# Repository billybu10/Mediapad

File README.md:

# Mediapad

Mediapad is an 8 key macropad with a two rotary encoders, an OLED Display. It uses QMK firmware

It focuses on media control and launching programs.

## CAD Model:
It has 2 separate printed pieces. The base where the PCB sits and the top cover.

Made in Fusion360.

## PCB
PCB made in KiCad.

Schematic

PCB

## Firmware Overview
This hackpad uses [QMK](https://qmk.fm/) firmware for everything. 

- the rotary encoders change volume and brightness
- The 8 keys
  
Mute | Play/Pause | Previous track | Next Track 
---|---|---|---
Calculator | Web browser | E-mail | Control Panel

## BOM:
Here should be everything you need to make this hackpad

- 8x Cherry MX Switches
- 8x DSA Keycaps
- 8x 1N4148 DO-35 Diodes.
- 2x EC11 Rotary Encoder
- 1x XIAO RP2040
- 1x Case (2 3d printed parts)

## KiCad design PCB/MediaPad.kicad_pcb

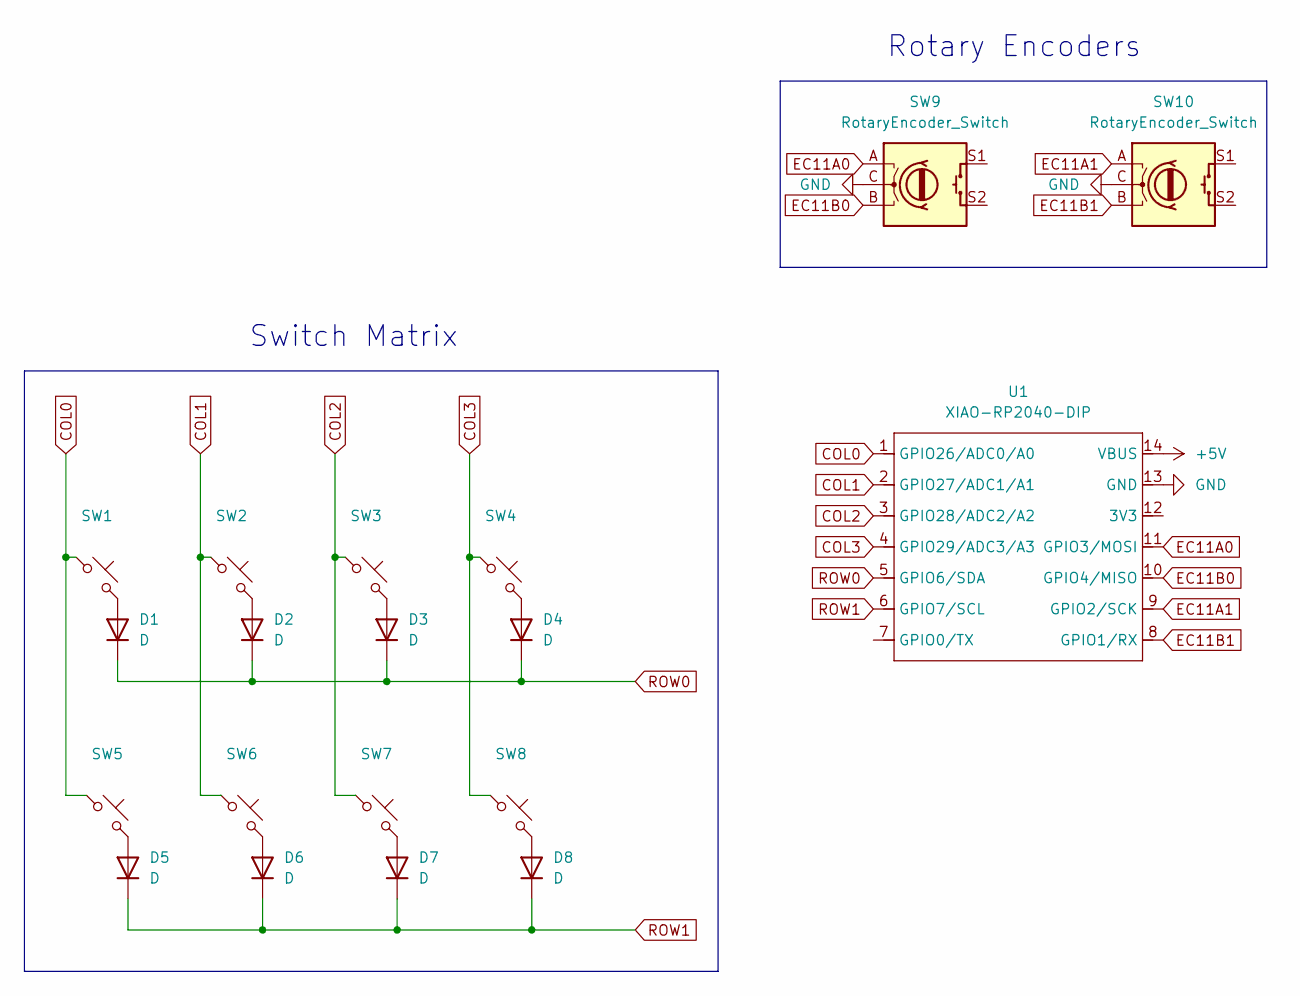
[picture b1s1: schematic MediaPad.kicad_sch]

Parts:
D1, D2, D3, D4, D5, D6, D7, D8: D; D_DO-35_SOD27_P3.81mm_Vertical_KathodeUp
SW1, SW2, SW3, SW4, SW5, SW6, SW7, SW8: SW_Cherry_MX_1.00u_PCB
SW9, SW10: RotaryEncoder_Switch; RotaryEncoder_Alps_EC11E-Switch_Vertical_H20mm_CircularMoun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
U1: XIAO-RP2040-DIP

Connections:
+5V: U1.14 (VBUS)
COL0: SW1.1, SW5.1, U1.1 (GPIO26/ADC0/A0)
COL1: SW2.1, SW6.1, U1.2 (GPIO27/ADC1/A1)
COL2: SW3.1, SW7.1, U1.3 (GPIO28/ADC2/A2)
COL3: SW4.1, SW8.1, U1.4 (GPIO29/ADC3/A3)
EC11A0: SW9.A, U1.11 (GPIO3/MOSI)
EC11A1: SW10.A, U1.9 (GPIO2/SCK)
EC11B0: SW9.B, U1.10 (GPIO4/MISO)
EC11B1: SW10.B, U1.8 (GPIO1/RX)
GND: SW9.C, SW10.C, U1.13 (GND)
unnamed: D1.2 (A), SW1.2
unnamed: D2.2 (A), SW2.2
unnamed: D3.2 (A), SW3.2
unnamed: D4.2 (A), SW4.2
unnamed: D5.2 (A), SW5.2
unnamed: D6.2 (A), SW6.2
unnamed: D7.2 (A), SW7.2
unnamed: D8.2 (A), SW8.2
ROW0: D1.1 (K), D2.1 (K), D3.1 (K), D4.1 (K), U1.5 (GPIO6/SDA)
ROW1: D5.1 (K), D6.1 (K), D7.1 (K), D8.1 (K), U1.6 (GPIO7/SCL)

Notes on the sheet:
Rotary Encoders
Switch Matrix

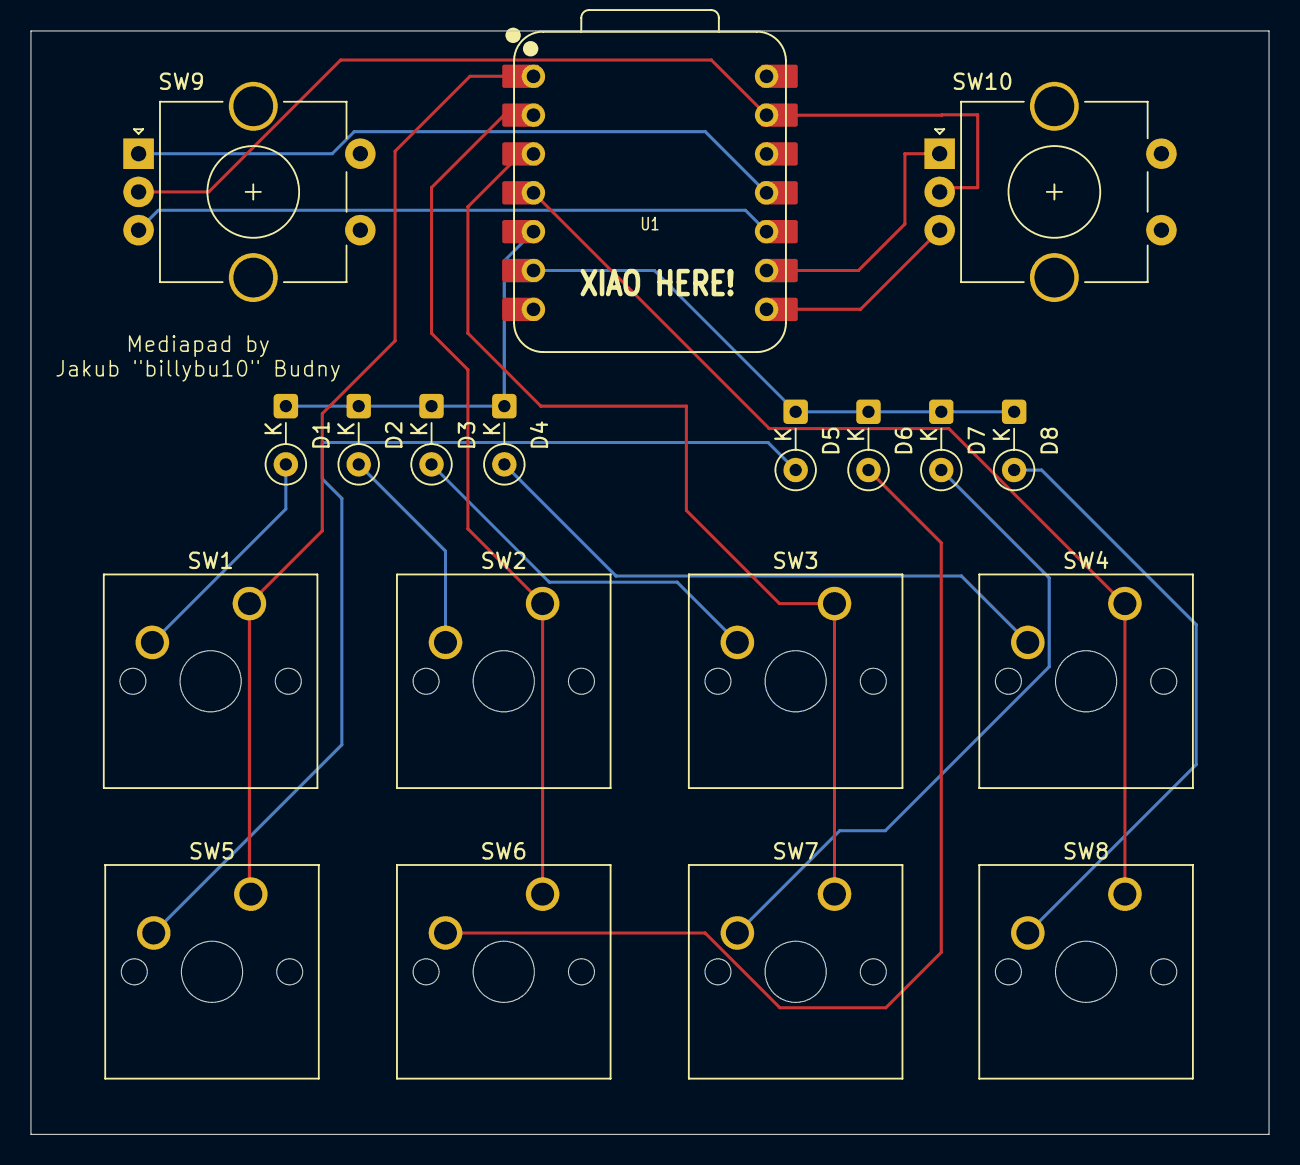
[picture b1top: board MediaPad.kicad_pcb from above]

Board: 2 copper layers, 81.0 x 72.2 mm, 19 parts (0 on the bottom side), 19 nets.

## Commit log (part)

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2025-07-28 add library
